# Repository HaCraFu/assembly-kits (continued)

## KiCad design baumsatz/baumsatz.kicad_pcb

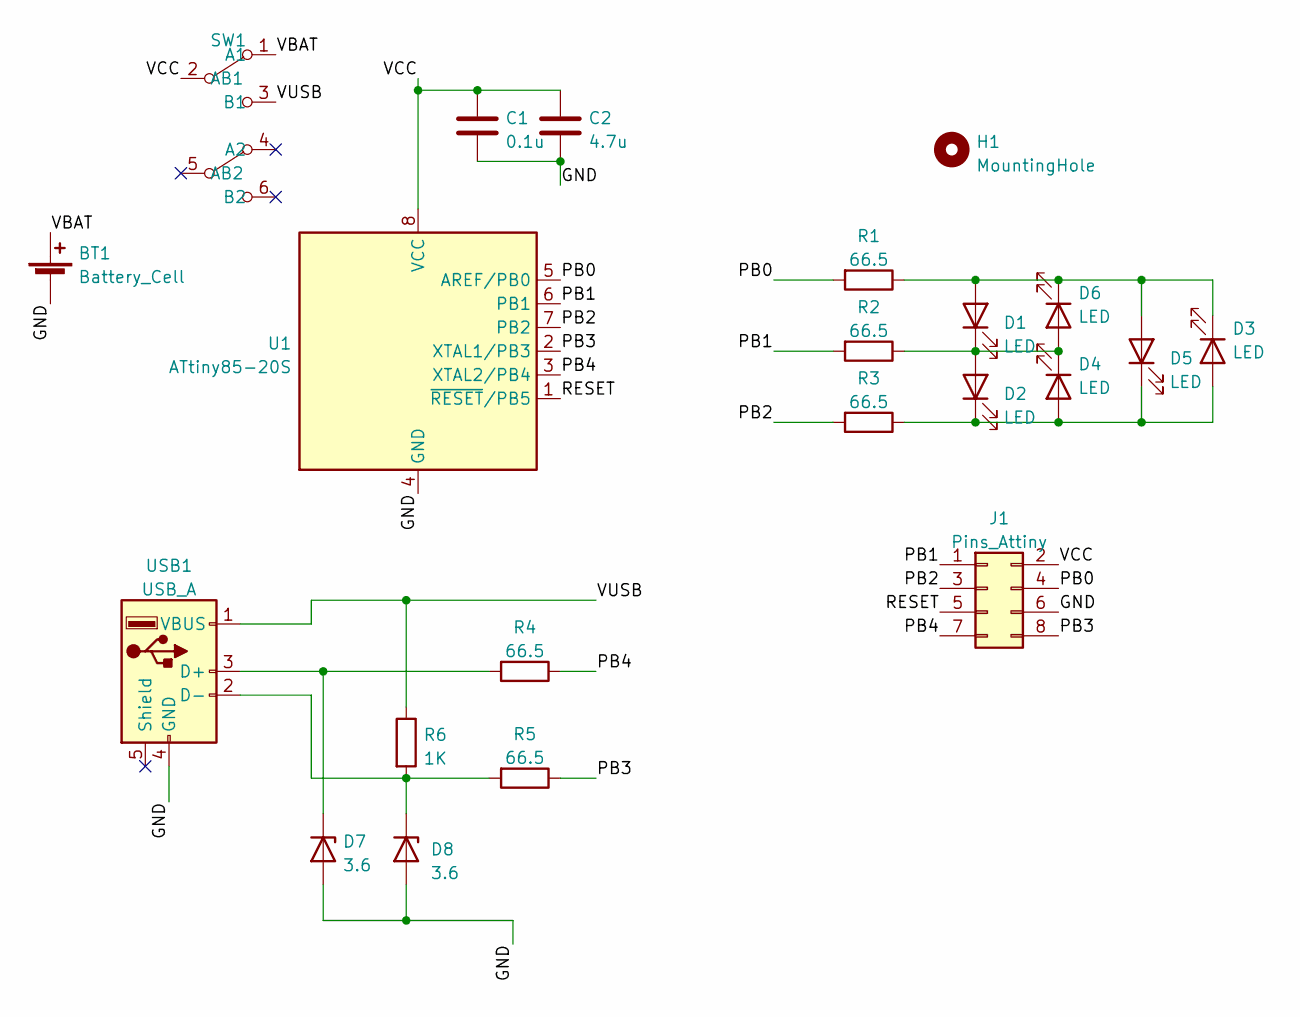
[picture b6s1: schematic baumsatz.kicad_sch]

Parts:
BT1: Battery_Cell; Batteryholder
C1: 0.1u; C_1206_3216Metric_Pad1.33x1.80mm_HandSolder
C2: 4.7u; C_1206_3216Metric_Pad1.33x1.80mm_HandSolder
D1, D2, D3, D4, D5, D6: LED; LED_1206
D7, D8: 3.6; Z-Diode Minimelf
H1: MountingHole; MountingHole_3.2mm_M3
J1: Pins_Attiny; PinHeader_2x04_Attiny
R1, R2, R3, R4, R5: 66.5; R_1206_3216Metric_Pad1.30x1.75mm_HandSolder
R6: 1K; R_1206_3216Metric_Pad1.30x1.75mm_HandSolder
SW1: SW_SPST; Switch_MSS22D18
U1: ATtiny85-20S; SOIC-8W_5.3x5.3mm_P1.27mm-breiter
USB1: USB_A; usb-PCB

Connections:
/GND: BT1.2 (-), C1.2, C2.2, D7.2 (A), D8.2 (A), J1.6, U1.4 (GND), USB1.4 (GND)
/PB0: J1.4, R1.2, U1.5 (AREF/PB0)
/PB1: J1.1, R2.2, U1.6 (PB1)
/PB2: J1.3, R3.2, U1.7 (PB2)
/PB3: J1.8, R5.1, U1.2 (XTAL1/PB3)
/PB4: J1.7, R4.1, U1.3 (XTAL2/PB4)
/RESET: J1.5, U1.1 (~RESET/PB5)
/VBAT: BT1.1 (+), SW1.1 (A1)
/VCC: C1.1, C2.1, J1.2, SW1.2 (AB1), U1.8 (VCC)
/VUSB: R6.1, SW1.3 (B1), USB1.1 (VBUS)
unnamed: D1.2 (A), D3.1 (K), D5.2 (A), D6.1 (K), R1.1
unnamed: D1.1 (K), D2.2 (A), D4.1 (K), D6.2 (A), R2.1
unnamed: D2.1 (K), D3.2 (A), D4.2 (A), D5.1 (K), R3.1
unnamed: D7.1 (K), R4.2, USB1.3 (D+)
unnamed: D8.1 (K), R5.2, R6.2, USB1.2 (D-)

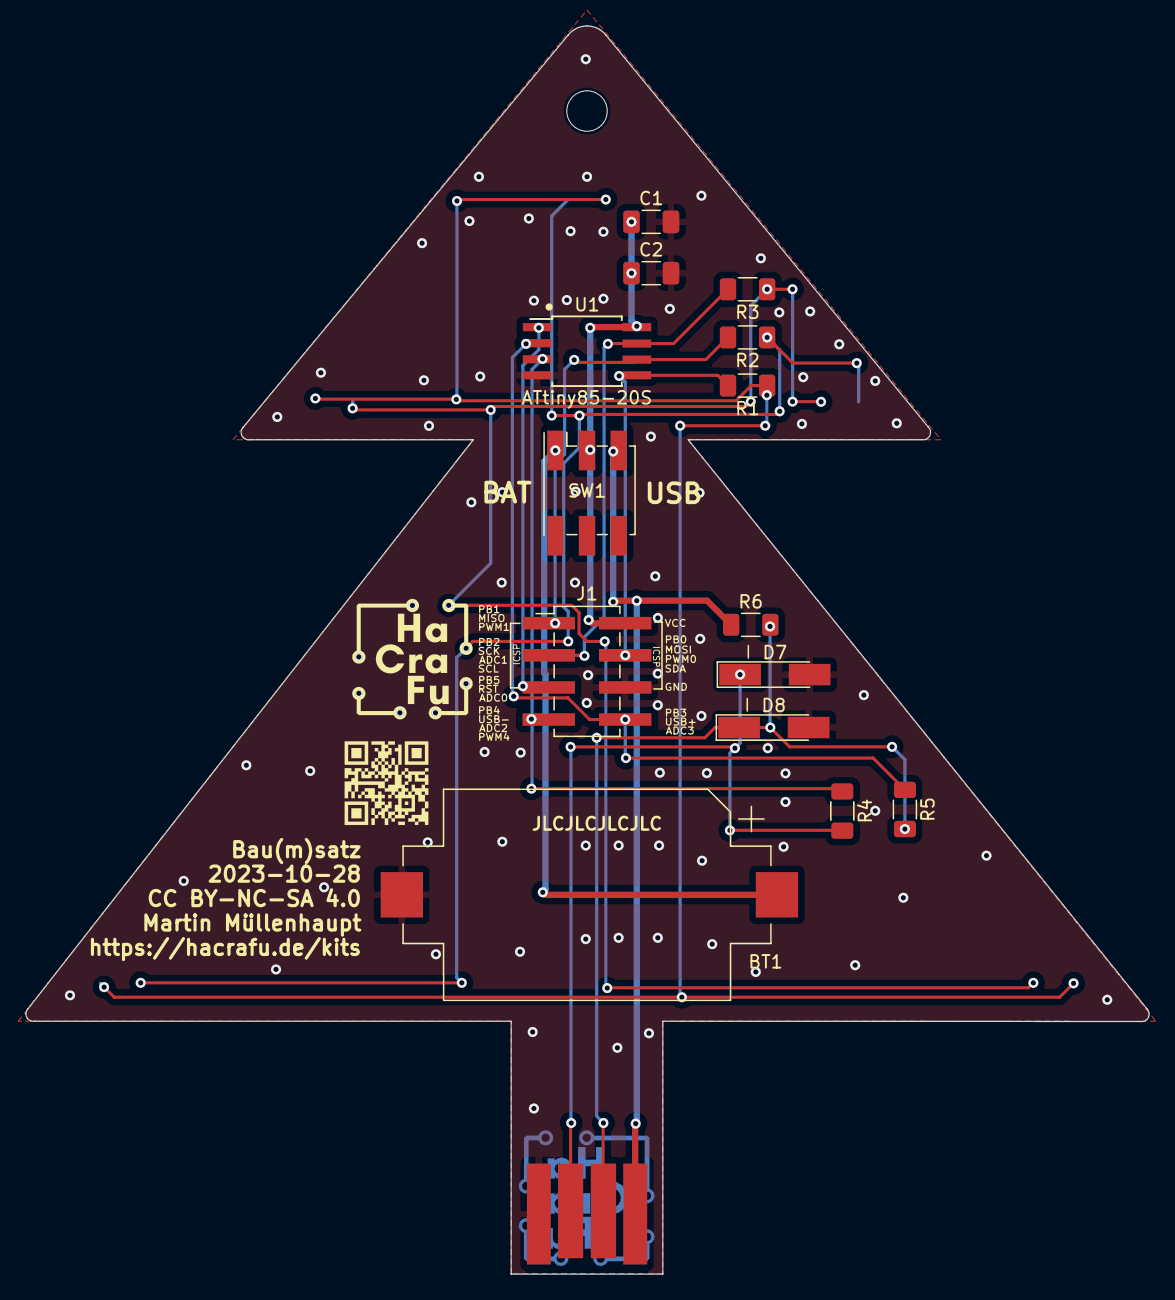
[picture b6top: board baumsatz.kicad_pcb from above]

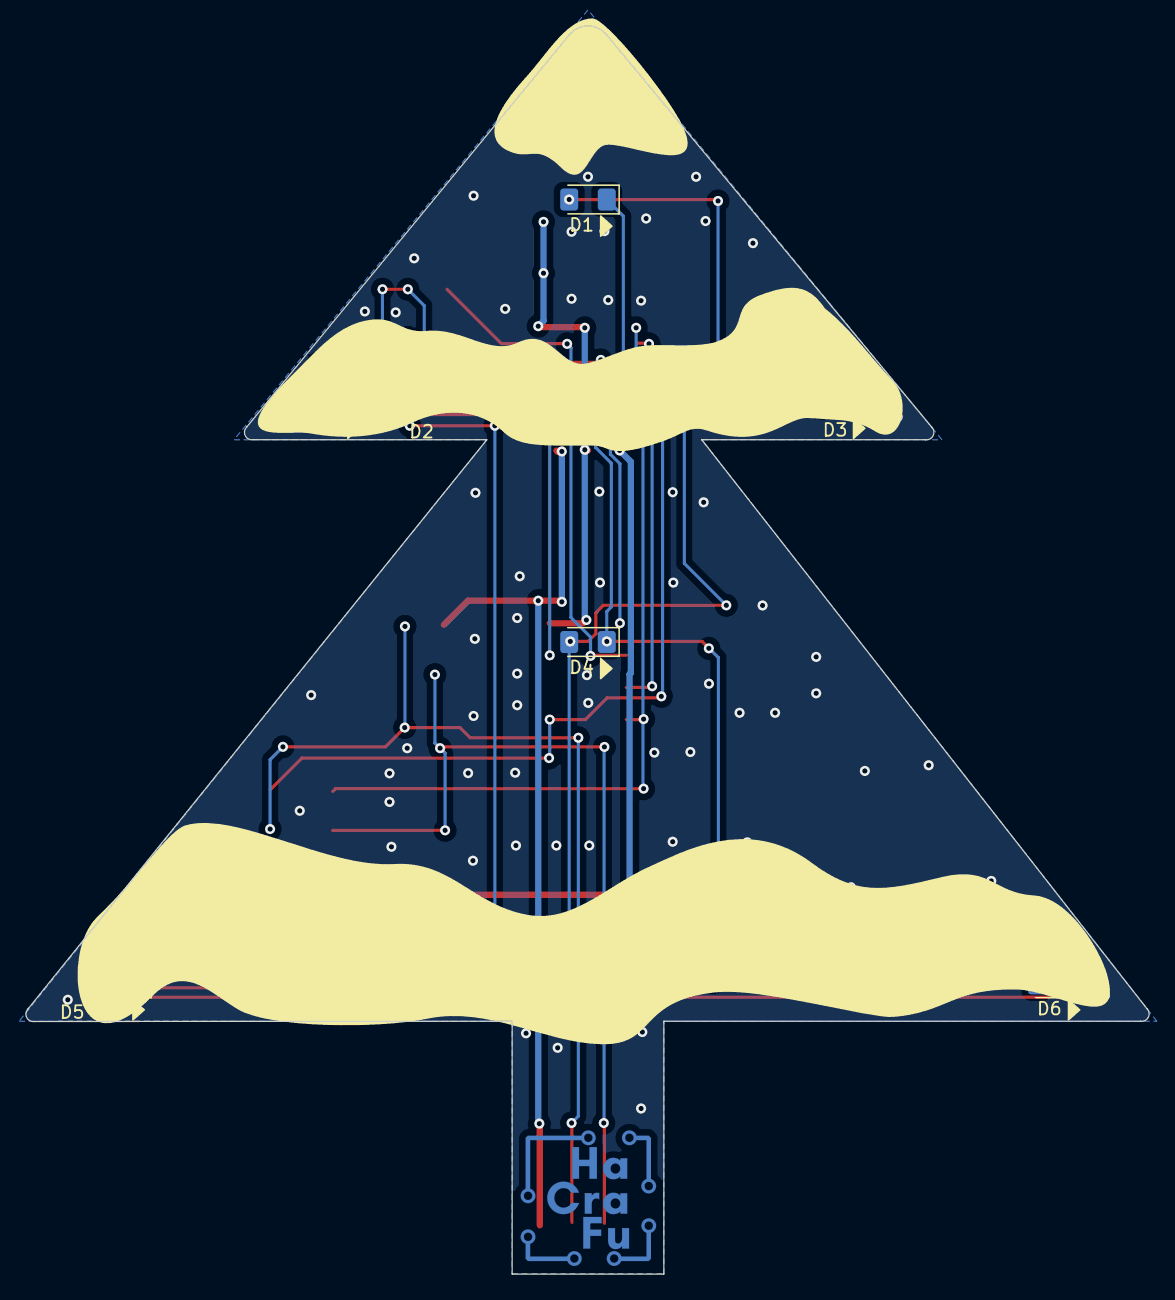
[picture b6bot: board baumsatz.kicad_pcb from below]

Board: 2 copper layers, 88.8 x 98.7 mm, 22 parts (6 on the bottom side), 15 nets.

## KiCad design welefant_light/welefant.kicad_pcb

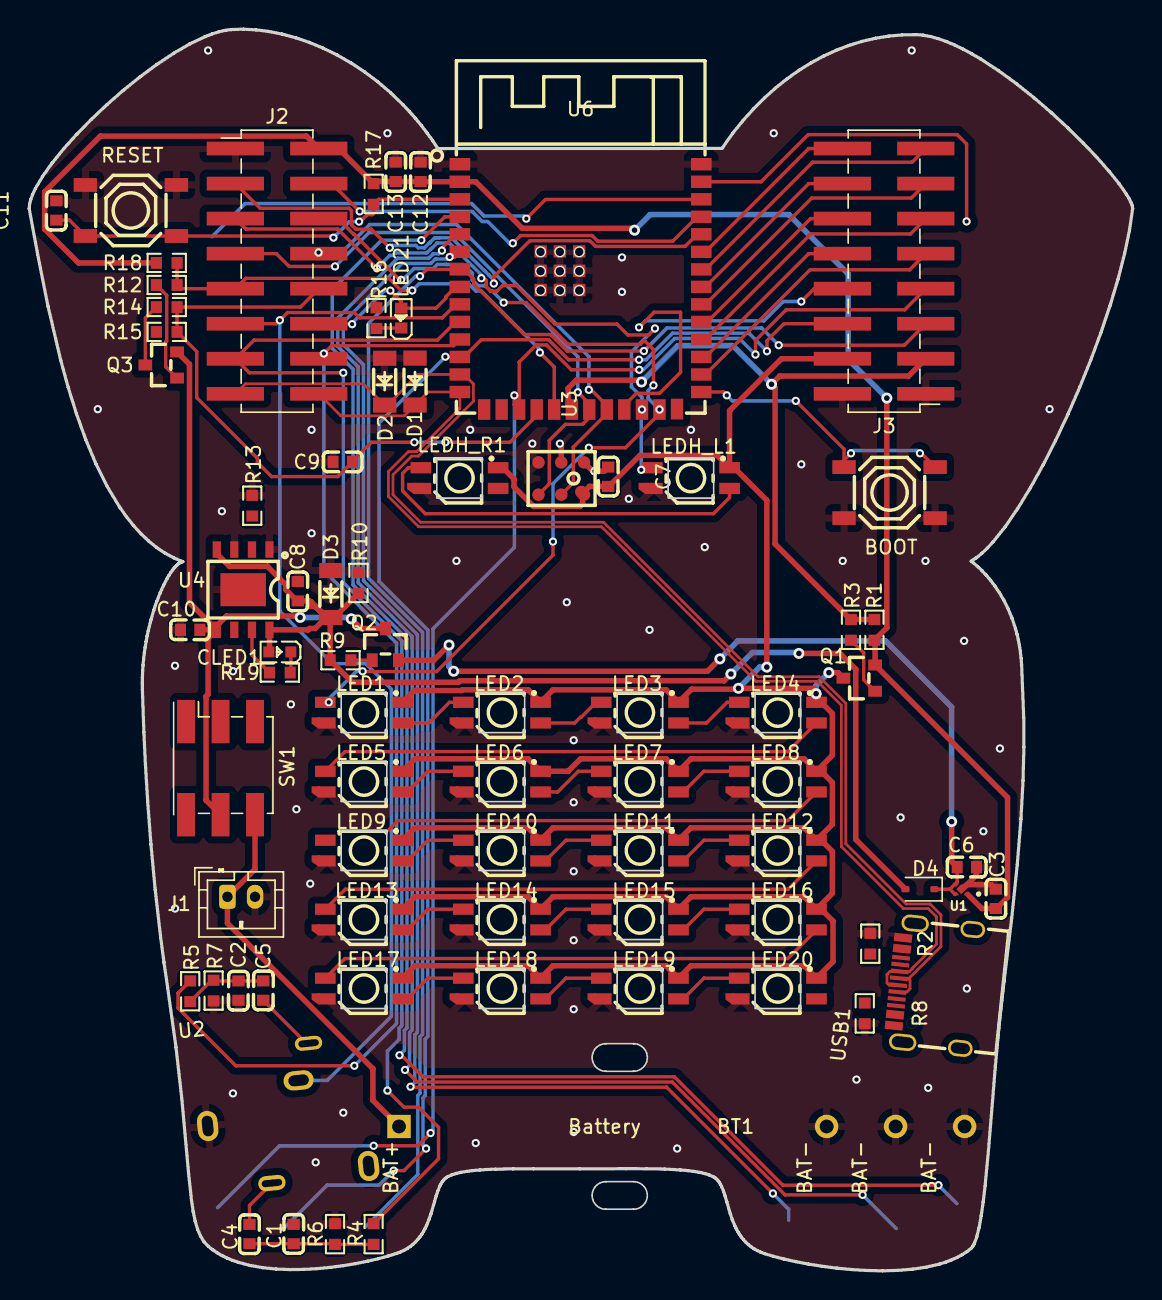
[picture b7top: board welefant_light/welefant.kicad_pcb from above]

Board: 2 copper layers, 80.0 x 90.0 mm, 76 parts (1 on the bottom side), 75 nets.

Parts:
BT1: Battery; LiPo_Recycled
C1, C2: 33n; C0603
C3, C6, C11: 1u; C0603
C4, C5, C8, C9, C10: 10u; C0603
C7, C12: 100n; C0603
C13: 22u; C0603
CLED1: yellow; LED0603-RD-YELLOW
D1, D2: 3V3; LL-34_L3.5-W1.5-RD
D3: 5V6; LL-34_L3.5-W1.5-RD
D4: 1N5819WS; D_SOD-323
J1: Conn_01x02; JST_PH_B2B-PH-K_1x02_P2.00mm_Vertical
J2: Conn_02x8_Odd_Even; PinHeader_2x08_P2.54mm_Vertical_SMD_handsolder
J3: Conn_02x11_Odd_Even; PinHeader_2x08_P2.54mm_Vertical_SMD_handsolder
LED1, LED2, LED3, LED4, LED5, LED6, LED7, LED8, LED9, LED10, LED11, LED12, LED13, LED14, LED15, LED16, LED17, LED18, LED19, LED20: SK6812MINI-E; SK6812MINI-E-handsolder
LED21: blue; LED0603-FD_BLUE
LEDH_L1: SK6812MINI-E; SK6812MINI-E-handsolder
LEDH_R1: SK6812MINI-E; SK6812MINI-E-handsolder
Q1, Q2, Q3: AO3401A; SOT-23_L2.9-W1.3-P1.90-LS2.4-BR
R1, R10, R17, R18: 10K; R0603
R2, R8: 5.1K; R0603
R3, R9, R12: 1K; R0603
R4, R5: 270; R0603
R6, R7: 150; R0603
R13: 3K3; R0603_NEW
R14: 390K; R0603
R15: 100K; R0603
R16, R19: 330; R0603
SW1: DPDT; Switch_MSS22D18
SW2: RESET; SW-SMD_4P-L5.1-W5.1-P3.70-LS6.5-TL-2
SW3: BOOT; SW-SMD_4P-L5.1-W5.1-P3.70-LS6.5-TL-2
U1: NCP167BMX330TBG; XDFN-4
U2: Audio Jack PJ-324; AUDIO-TH_PJ-32400
U3: GSA4737H12-F26-6P; MIC-SMD_GSA4737H12-F26-6P
U4: TP4056; ESOP-8_L4.9-W3.9-P1.27-LS6.0-BL-EP
U5: welefant
U6: ESP32-S3-WROOM-1(N16R2); WIRELM-SMD_ESP32-S3-WROOM-1
USB1: USB-TYPE-C-018; USB-C_SMD-TYPE-C-31-M-12

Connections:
/AUDIO_PWM_L: J2.13, R4.1, U6.10 (IO17)
/AUDIO_PWM_R: J2.14, R5.1, U6.11 (IO18)
/BAT_SENS: C9.2, J2.10, R14.1, R15.1, U6.18 (IO10)
/BAT_SENS_EN: J2.9, R12.2, R18.2, U6.19 (IO11)
/D1_LED: LED4.2 (DOUT), LED5.4 (DIN)
/D2_LED: LED8.2 (DOUT), LED9.4 (DIN)
/D3_LED: LED12.2 (DOUT), LED13.4 (DIN)
/D4_LED: LED16.2 (DOUT), LED17.4 (DIN)
/IO0: SW3.1 (A), SW3.2 (B), U6.27 (IO0)
/IO21: J3.8, U6.23 (IO21)
/IO35: J3.9, U6.28 (IO35)
/IO36: J3.10, U6.29 (IO36)
/IO37: J3.11, U6.30 (IO37)
/IO38: J3.12, U6.31 (IO38)
/IO39: J3.13, U6.32 (IO39)
/IO40: J3.14, U6.33 (IO40)
/IO41: J3.15, U6.34 (IO41)
/IO42: J3.16, U6.35 (IO42)
/JACK_SENS: J2.11, U2.3, U6.9 (IO16)
/LED: J2.12, LED21.2 (A), U6.8 (IO15)
/LED_HEAD: J2.5, LEDH_L1.4 (DIN), U6.24 (IO47)
/LED_MATRIX: J2.6, LED1.4 (DIN), U6.25 (IO48)
/MIC_CLK: J2.7, U3.4 (CLOCK), U6.21 (IO13)
/MIC_DATA: J2.8, U3.5 (DATA), U6.22 (IO14)
/RESET: C11.1, R17.2, SW2.1 (A), SW2.2 (B), U6.3 (EN)
/RX: J2.3, U6.36 (RXD0)
/TOUCH_EL: U5.1 (EarL), U6.39 (IO1)
/TOUCH_ER: U5.2 (EarR), U6.38 (IO2)
/TOUCH_T1: U5.3 (Toe1), U6.4 (IO4)
/TOUCH_T2: U5.4 (Toe2), U6.5 (IO5)
/TOUCH_T3: U5.5 (Toe3), U6.6 (IO6)
/TOUCH_T4: J3.5, U5.6 (Toe4), U6.7 (IO7)
/TOUCH_T5: J3.6, U5.7 (Toe5), U6.12 (IO8)
/TOUCH_T6: J3.7, U5.8 (Toe6), U6.17 (IO9)
/TX: J2.4, U6.37 (TXD0)
/USB_DN: D2.1 (C), J2.15, U6.13 (IO19), USB1.A7 (DN1), USB1.B7 (DN2)
/USB_DP: D1.1 (C), J2.16, U6.14 (IO20), USB1.A6 (DP1), USB1.B6 (DP2)
/V5: C8.1, CLED1.2 (A), D3.1 (C), D4.2 (A), R9.2, R10.2, U4.4 (VCC), U4.8 (CE), USB1.A4 (VBUS), USB1.A9 (VBUS), USB1.B4 (VBUS), USB1.B9 (VBUS)
/V33: C3.2, C12.1, C13.1, J2.2, Q1.2 (S), R1.1, R17.1, R18.1, U1.1 (OUT), U6.2 (3V3)
/VBAT: C10.2, Q2.3 (D), Q3.2 (S), SW1.5 (AB2), U4.5 (BAT)
/VBUS: C6.1, D4.1 (K), Q2.2 (S), U1.3 (EN), U1.4 (IN)
/VEXT: C7.2, J3.4, LED1.1 (VDD), LED2.1 (VDD), LED3.1 (VDD), LED4.1 (VDD), LED5.1 (VDD), LED6.1 (VDD), LED7.1 (VDD), LED8.1 (VDD), LED9.1 (VDD), LED10.1 (VDD), LED11.1 (VDD), LED12.1 (VDD), LED13.1 (VDD), LED14.1 (VDD), LED15.1 (VDD), LED16.1 (VDD), LED17.1 (VDD), LED18.1 (VDD), LED19.1 (VDD), LED20.1 (VDD), LEDH_L1.1 (VDD), LEDH_R1.1 (VDD), Q1.3 (D), U3.6 (VDD)
/VEXT_EN: J3.3, R1.2, R3.2, U6.20 (IO12)
GND: BT1.2 (-), C1.1, C2.1, C3.1, C6.2, C7.1, C8.2, C9.1, C10.1, C11.2, C12.2, C13.2, D1.2 (A), D2.2 (A), D3.2 (A), J1.2, J2.1, J3.1, J3.2, LED1.3 (GND), LED2.3 (GND), LED3.3 (GND), LED4.3 (GND), LED5.3 (GND), LED6.3 (GND), LED7.3 (GND), LED8.3 (GND), LED9.3 (GND), LED10.3 (GND), LED11.3 (GND), LED12.3 (GND), LED13.3 (GND), LED14.3 (GND), LED15.3 (GND), LED16.3 (GND), LED17.3 (GND), LED18.3 (GND), LED19.3 (GND), LED20.3 (GND), LEDH_L1.3 (GND), LEDH_R1.3 (GND), R2.1, R6.1, R7.1, R8.2, R10.1, R13.2, R15.2, R16.1, SW2.3 (C), SW2.4 (D), SW3.3 (C), SW3.4 (D), U1.2 (GND), U1.5 (EPAD), U2.1, U3.1 (GND), U3.2 (SELECT), U3.3 (GND), U4.1 (TEMP), U4.3 (GND), U4.9 (EP), U6.1 (GND), U6.40 (GND), U6.41 (GND), USB1.A1 (GND), USB1.A12 (GND), USB1.B1 (GND), USB1.B12 (GND)
unnamed: BT1.1 (+), J1.1, SW1.6 (B2)
unnamed: C1.2, C4.1, R4.2, R6.2
unnamed: C2.2, C5.1, R5.2, R7.2
unnamed: C4.2, U2.5
unnamed: C5.2, U2.2
unnamed: CLED1.1 (C), R19.1
unnamed: LED1.2 (DOUT), LED2.4 (DIN)
unnamed: LED2.2 (DOUT), LED3.4 (DIN)
unnamed: LED3.2 (DOUT), LED4.4 (DIN)
unnamed: LED5.2 (DOUT), LED6.4 (DIN)
unnamed: LED6.2 (DOUT), LED7.4 (DIN)
unnamed: LED7.2 (DOUT), LED8.4 (DIN)
unnamed: LED9.2 (DOUT), LED10.4 (DIN)
unnamed: LED10.2 (DOUT), LED11.4 (DIN)
unnamed: LED11.2 (DOUT), LED12.4 (DIN)
unnamed: LED13.2 (DOUT), LED14.4 (DIN)
unnamed: LED14.2 (DOUT), LED15.4 (DIN)
unnamed: LED15.2 (DOUT), LED16.4 (DIN)
unnamed: LED17.2 (DOUT), LED18.4 (DIN)
unnamed: LED18.2 (DOUT), LED19.4 (DIN)
unnamed: LED19.2 (DOUT), LED20.4 (DIN)
unnamed: LED21.1 (C), R16.2
unnamed: LEDH_L1.2 (DOUT), LEDH_R1.4 (DIN)
unnamed: Q1.1 (G), R3.1
unnamed: Q2.1 (G), R9.1
unnamed: Q3.3 (D), R14.2
unnamed: Q3.1 (G), R12.1
unnamed: R13.1, U4.2 (PROG)
unnamed: R19.2, U4.7 (~CHRG)
unnamed: R8.1, USB1.A5 (CC1)
unnamed: R2.2, USB1.B5 (CC2)

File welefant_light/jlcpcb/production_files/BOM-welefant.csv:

Comment,Designator,Footprint,LCSC
100n,"C12,C7",C0603,C14663
AO3401A,"Q1,Q2,Q3",SOT-23_L2.9-W1.3-P1.90-LS2.4-BR,C15127
1u,"C11,C3,C6",C0603,C15849
TP4056,U4,ESOP-8_L4.9-W3.9-P1.27-LS6.0-BL-EP,C16581
10u,"C10,C4,C5,C8,C9",C0603,C19702
33n,"C1,C2",C0603,C21117
1K,"R12,R3,R9",R0603,C21190
150,"R6,R7",R0603,C22808
270,"R4,R5",R0603,C22966
3K3,R13,R0603_NEW,C22978
330,"R16,R19",R0603,C23138
390K,R14,R0603,C23150
5.1K,"R2,R8",R0603,C23186
100K,R15,R0603,C25803
10K,"R1,R10,R17,R18",R0603,C25804
Audio Jack PJ-324,U2,AUDIO-TH_PJ-32400,C2884956
ESP32-S3-WROOM-1(N16R2),U6,WIRELM-SMD_ESP32-S3-WROOM-1,C2913205
USB-TYPE-C-018,USB1,USB-C_SMD-TYPE-C-31-M-12,C2927038
RESET,"SW2,SW3",SW-SMD_4P-L5.1-W5.1-P3.70-LS6.5-TL-2,C318884
GSA4737H12-F26-6P,U3,MIC-SMD_GSA4737H12-F26-6P,C5142171
SK6812MINI-E,"LED1,LED10,LED11,LED12,LED13,LED14,LED15,LED16,LED17,LED18,LED19,LED2,LED20,LED3,LED4,LED5,LED6,LED7,LED8,LED9,LEDH_L1,LEDH_R1",SK6812MINI-E-handsolder,C5149201
22u,C13,C0603,C59461
yellow,CLED1,LED0603-RD-YELLOW,C72038
blue,LED21,LED0603-FD_BLUE,C72041
3V3,"D1,D2",LL-34_L3.5-W1.5-RD,C8056
5V6,D3,LL-34_L3.5-W1.5-RD,C8062
NCP167BMX330TBG,U1,XDFN-4,C892227
Conn_01x02,J1,JST_PH_B2B-PH-K_1x02_P2.00mm_Vertical,
Conn_02x6_Odd_Even,J3,PinHeader_2x06_P2.54mm_Vertical_SMD_handsolder,
Conn_02x8_Odd_Even,J2,PinHeader_2x08_P2.54mm_Vertical_SMD_handsolder,
1N5819WS,D4,D_SOD-323,
Battery,BT1,LiPo_Recycled_welefant,
DPDT,SW1,Switch_MSS22D18,
welefant,U5,welefant,

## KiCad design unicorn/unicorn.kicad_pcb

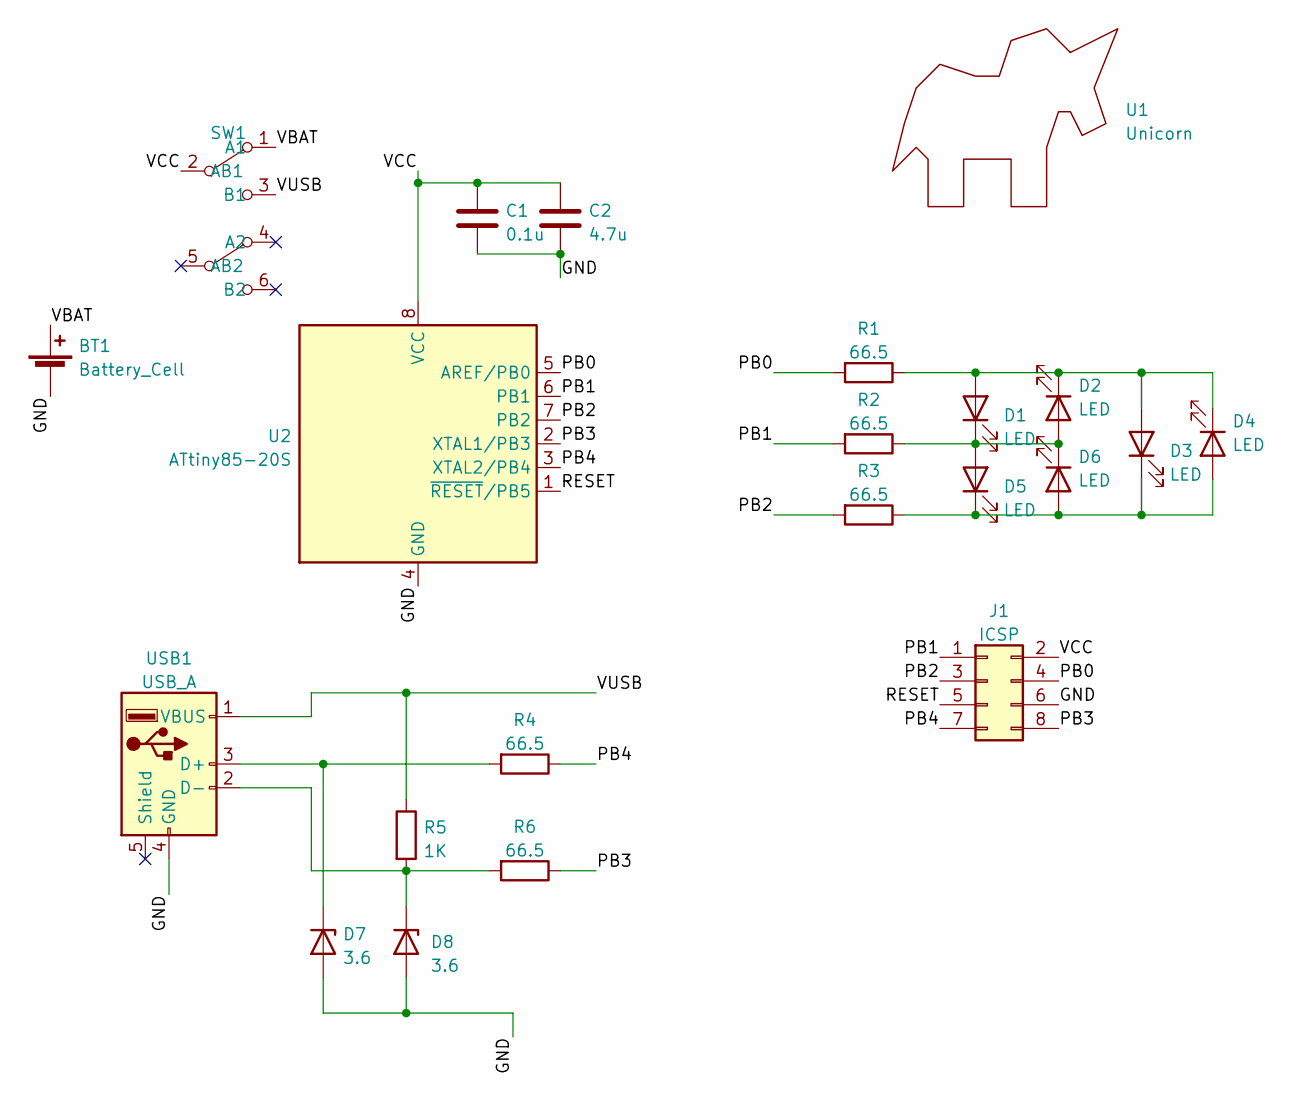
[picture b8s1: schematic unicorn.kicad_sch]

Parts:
BT1: Battery_Cell; Batteryholder
C1: 0.1u; C_1206_3216Metric_Pad1.33x1.80mm_HandSolder
C2: 4.7u; C_1206_3216Metric_Pad1.33x1.80mm_HandSolder
D1, D2, D3, D4, D5, D6: LED; 5mm_SMD-Pad
D7, D8: 3.6; Z-Diode Minimelf
J1: ICSP; PinHeader
R1, R2, R3, R4, R6: 66.5; R_1206_3216Metric_Pad1.30x1.75mm_HandSolder
R5: 1K; R_1206_3216Metric_Pad1.30x1.75mm_HandSolder
SW1: SW_SPST; Switch_MSS22D18
U1: Unicorn; unicorn
U2: ATtiny85-20S; SOIC-8W_5.3x5.3mm_P1.27mm-breiter
USB1: USB_A; usb-PCB

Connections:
/GND: BT1.2 (-), C1.2, C2.2, D7.2 (A), D8.2 (A), J1.6, U2.4 (GND), USB1.4 (GND)
/PB0: J1.4, R1.2, U2.5 (AREF/PB0)
/PB1: J1.1, R2.2, U2.6 (PB1)
/PB2: J1.3, R3.2, U2.7 (PB2)
/PB3: J1.8, R6.1, U2.2 (XTAL1/PB3)
/PB4: J1.7, R4.1, U2.3 (XTAL2/PB4)
/RESET: J1.5, U2.1 (~RESET/PB5)
/VBAT: BT1.1 (+), SW1.1 (A1)
/VCC: C1.1, C2.1, J1.2, SW1.2 (AB1), U2.8 (VCC)
/VUSB: R5.1, SW1.3 (B1), USB1.1 (VBUS)
unnamed: D1.1 (K), D2.2 (A), D5.2 (A), D6.1 (K), R2.1
unnamed: D1.2 (A), D2.1 (K), D3.2 (A), D4.1 (K), R1.1
unnamed: D3.1 (K), D4.2 (A), D5.1 (K), D6.2 (A), R3.1
unnamed: D7.1 (K), R4.2, USB1.3 (D+)
unnamed: D8.1 (K), R5.2, R6.2, USB1.2 (D-)

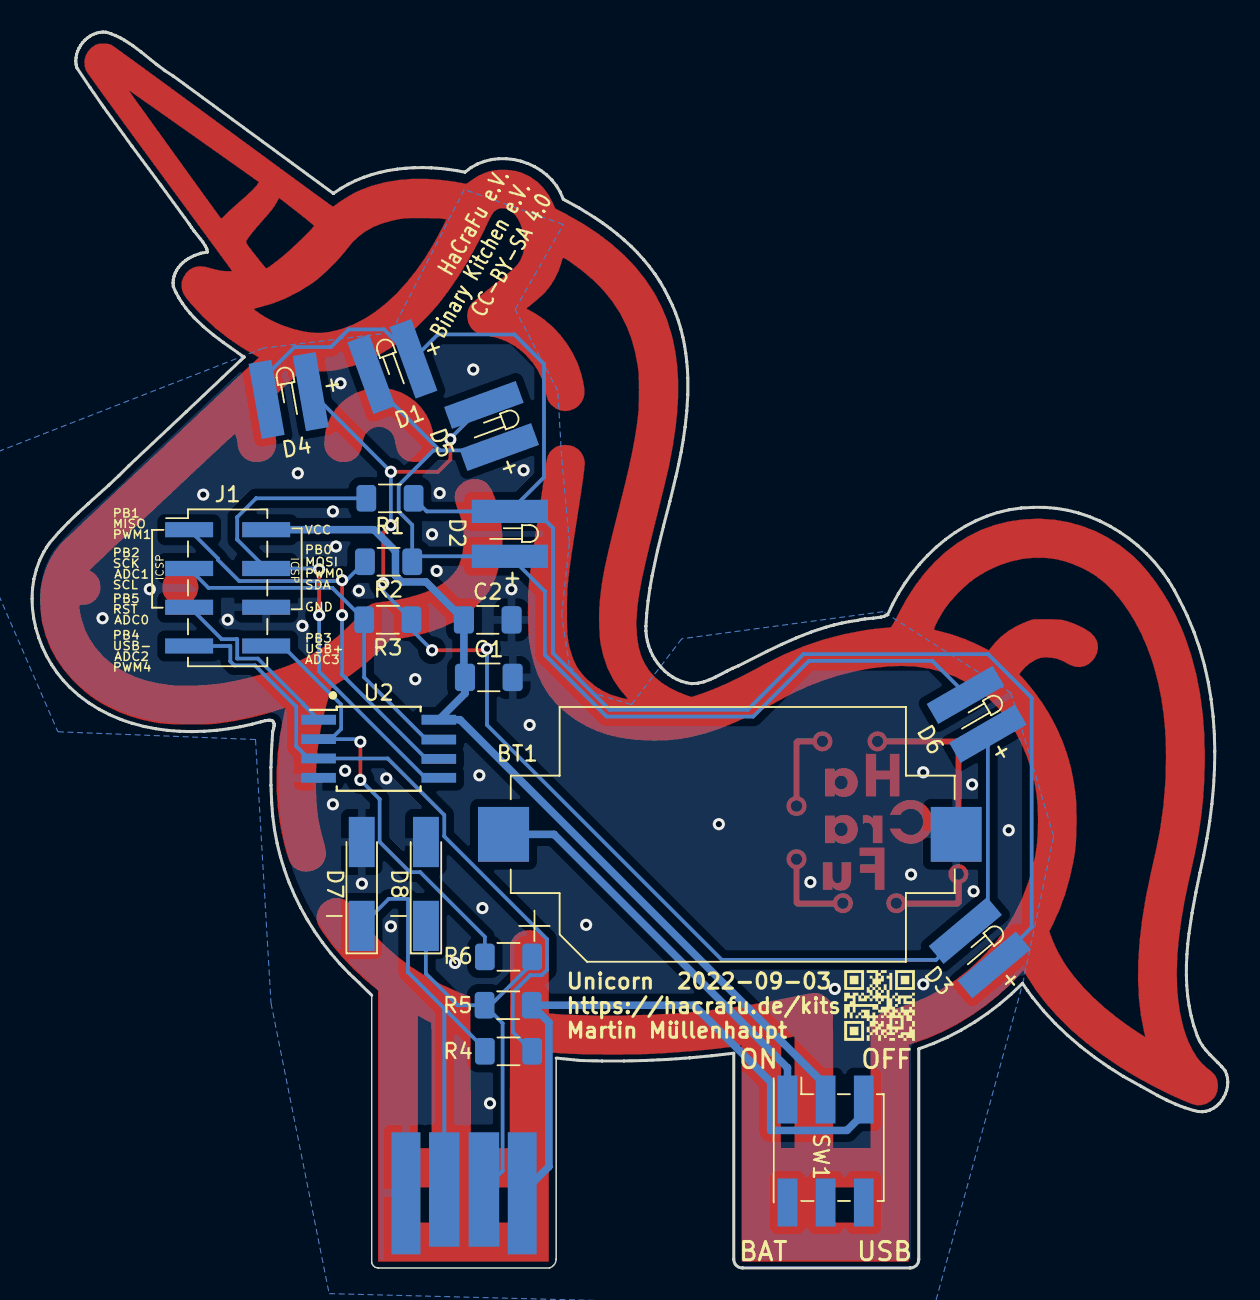
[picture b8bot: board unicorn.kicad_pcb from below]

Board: 2 copper layers, 78.4 x 81.0 mm, 22 parts (21 on the bottom side), 15 nets.

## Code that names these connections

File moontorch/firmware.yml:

esphome:
    name: moontorch1

external_components:
  - source:
      type: local
      path: custom_components

ota:
  platform: esphome

api:

esp32:
  board: adafruit_qtpy_esp32c3
  framework:
    type: arduino

htct62radio:
  id: radio

wifi:
  ssid: ssid
  password: password

web_server:
  port: 80

logger:
  level: DEBUG
  

esp32_ble_tracker:
  on_ble_advertise:
    then:
      - lambda: |-
          ESP_LOGD("ble_adv", "New BLE device");
          ESP_LOGD("ble_adv", "  address: %s", x.address_str().c_str());
          ESP_LOGD("ble_adv", "  name: %s", x.get_name().c_str());
          ESP_LOGD("ble_adv", "  Advertised service UUIDs:");
          for (auto uuid : x.get_service_uuids()) {
              ESP_LOGD("ble_adv", "    - %s", uuid.to_string().c_str());
          }
          ESP_LOGD("ble_adv", "  Advertised service data:");
          for (auto data : x.get_service_datas()) {
              ESP_LOGD("ble_adv", "    - %s: (length %i)", data.uuid.to_string().c_str(), data.data.size());
          }
          ESP_LOGD("ble_adv", "  Advertised manufacturer data:");
          for (auto data : x.get_manufacturer_datas()) {
              ESP_LOGD("ble_adv", "    - %s: (length %i)", data.uuid.to_string().c_str(), data.data.size());
          }

interval:
  - interval: 10s
    then:
      - light.turn_off: light1
      - light.turn_off: light2
      - lambda: |-
          static constexpr auto minLat = static_cast<uint32_t>(52.53084314728766 * 1e4);
          static constexpr auto minLon = static_cast<uint32_t>(13.808012008666994 * 1e4);
          auto lat_ = static_cast<uint32_t>(id(lat).get_state()* 1e4);
          auto lon_ = static_cast<uint32_t>(id(lon).get_state()* 1e4);
          auto dlat = static_cast<uint32_t>(lat_ - minLat);
          auto dlon = static_cast<uint32_t>(lon_ - minLon);
          auto bat = static_cast<uint8_t>(id(battery)->get_state());

          id(radio)->transmit_packet({
            static_cast<uint8_t>((dlat >> 0) & 0xFF),
            static_cast<uint8_t>((dlat >> 8) & 0xFF),
            static_cast<uint8_t>((dlon >> 0) & 0xFF),
            static_cast<uint8_t>((dlon >> 8) & 0xFF),
            bat,
            1
            });

      - light.turn_on: light1
      - light.turn_on: light2
output:
  - platform: moonled
    pin: 
      number: GPIO6
      inverted: true
      mode:
        output: true
        open_drain: true
    id: led1
    frequency: 100000Hz
    # max_power: 10%
  - platform: moonled
    pin:
      number: GPIO7
      inverted: true
      mode:
        output: true
        open_drain: true
      # allow_other_uses: true
    id: led2
    frequency: 100000Hz
    # max_power: 10%

binary_sensor:
  - platform: gpio
    pin: 
      number: GPIO1
      mode:
        input: true
        pullup: true
      inverted: true
    filters:
      - delayed_on: 30ms
    name: "Torch Button"
    on_press:
      then:
        - light.turn_on: light1
        - light.turn_on: light2
    on_release:
      then:
        - light.turn_off: light1
        - light.turn_off: light2

sensor:
  - platform: adc
    pin: GPIO0
    attenuation: 12db
    update_interval: 60s
    device_class: battery
    unit_of_measurement: "%"
    name: "Battery Level"
    id: battery
    filters:
      - calibrate_linear:
          - 1.75 -> 0.0
          - 1.85 -> 12
          - 1.9 -> 40
          - 2 -> 78
          - 2.1 -> 100

light:
  - platform: monochromatic
    id: light1
    output: led1
    name: "Led White"
    default_transition_length: 0s
    restore_mode: RESTORE_DEFAULT_OFF
  - platform: monochromatic
    id: light2
    output: led2
    name: "Led Red"
    default_transition_length: 0s
    restore_mode: RESTORE_DEFAULT_OFF

uart:
  rx_pin: GPIO20
  tx_pin: GPIO21
  baud_rate: 9600

gps:
  update_interval: 4s
  latitude:
    name: "Latitude"
    id: lat
  longitude:
    name: "Longitude"
    id: lon

time:
  - platform: gps

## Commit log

2022-09-09 init
2022-09-09 firmware libs
2022-11-10 add windows setup videos
2023-02-26 start welefant
2023-08-08 welefant weiter
2023-08-10 blubb
2023-08-14 stand
2023-08-14 bestellt
2023-10-07 Revert "use S3FH4R2 / remove flash chip"
    This reverts commit b0f4cc23a485e26b2c676c6cda33926215215541.
2023-10-07 use S3FH4R2 / remove flash chip
2023-10-07 weiter
2023-10-07 weiter welefant umgestaltung ohne wroom
2023-10-07 muss jetzt auf ESP32-S3FH4R2 umstellen
2023-10-08 baumsatz update
2023-10-08 move footprints
2023-10-08 start owlthief
2023-10-11 welefant bestellung
2023-10-28 bestellung techniktag
2024-01-17 Deployed a6324d5 to latest with MkDocs 1.5.3 and mike 2.0.0
2024-01-17 Set default version to latest with mike 2.0.0
2024-01-17 Deployed a6324d5 to latest-de with MkDocs 1.5.3 and mike 2.0.0
2024-01-17 Removed latest with mike 2.0.0
2024-01-17 Deployed f2f84d8 to latest with MkDocs 1.5.3 and mike 2.0.0
2024-01-17 Removed latest-de with mike 2.0.0
2024-01-17 mkdocs
2024-01-17 fix readme
2024-01-17 Deployed 528c306 to latest with MkDocs 1.5.3 and mike 2.0.0
2024-01-19 Deployed 528c306 to 2022-08-12 with MkDocs 1.5.3 and mike 2.0.0
2024-01-19 more docs refactoring
2024-01-19 Deployed 7d27572 to latest with MkDocs 1.5.3 and mike 2.0.0
2024-01-19 add kibot artifacts
2024-01-19 Deployed 4adc743 to latest with MkDocs 1.5.3 and mike 2.0.0
2024-01-26 fix owlthief?
2024-01-26 welefant redesign
2024-01-26 improve owl thief
2025-02-03 add batterypack order
2025-05-18 welefant: add fuse and make LED cutout smaller
2025-05-18 stand bestellung 18.5.25
2025-06-13 weiter moontorch
2025-06-27 zwischenstand bestellfähig 1
2025-06-29 bestellung
2025-07-10 firmware stand
2025-07-10 pcb dnp
2026-01-20 moontorch 3d models ref
2026-01-20 moontorch schematic pin labels
2026-01-20 fix doc links
2026-01-20 Deployed c98774b to latest with MkDocs 1.6.1 and mike 2.1.3
2026-01-20 docs
